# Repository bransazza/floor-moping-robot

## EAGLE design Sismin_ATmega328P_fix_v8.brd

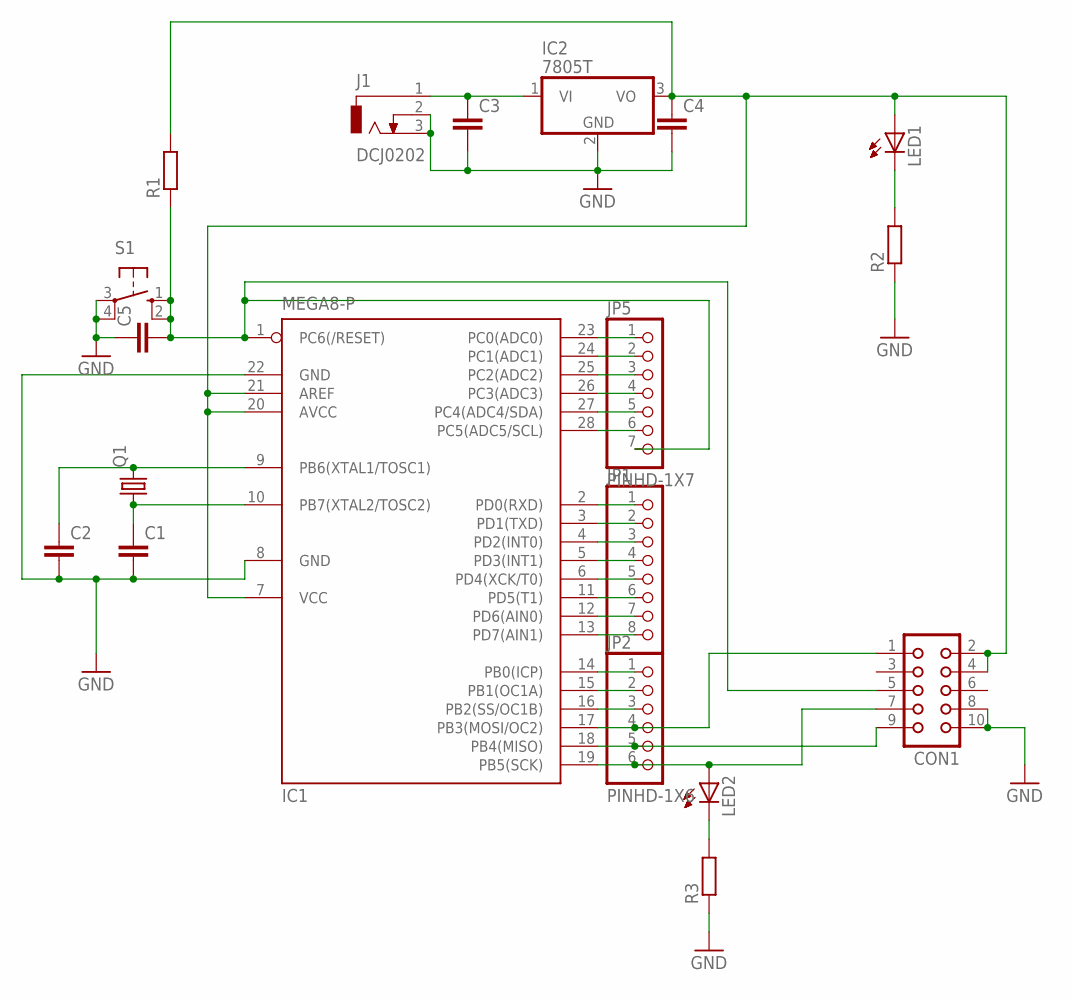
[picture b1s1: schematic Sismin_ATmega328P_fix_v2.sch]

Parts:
C1, C2, C3, C4, C5: C-EU025-030X050; C025-030X050
CON1: CON10
IC1: MEGA8-P; DIL28-3
IC2: 7805T; TO220H
J1: DCJ0202
JP1: PINHD-1X8; 1X08
JP2: PINHD-1X6; 1X06
JP5: PINHD-1X7; 1X07
LED1, LED2: LED3MM
Q1: CRYSTALHC49U-V; HC49U-V
R1, R2, R3: R-EU_0204/7; 0204/7
S1: 10-XX; B3F-10XX

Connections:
GND: C1.2, C2.2, C3.2, C4.2, C5.1, CON1.8, CON1.10, IC1.8 (GND), IC1.22 (GND), IC2.2 (GND), J1.2, J1.3, R2.1, R3.1, S1.3, S1.4 (P1)
unnamed: C3.1, IC2.1 (VI), J1.1
unnamed: C4.1, CON1.2, CON1.4, IC1.7 (VCC), IC1.20 (AVCC), IC1.21 (AREF), IC2.3 (VO), LED1.A, R1.2
unnamed: LED1.K (C), R2.2
unnamed: LED2.K (C), R3.2
unnamed: IC1.23 (PC0(ADC0)), JP5.1
unnamed: IC1.24 (PC1(ADC1)), JP5.2
unnamed: IC1.25 (PC2(ADC2)), JP5.3
unnamed: IC1.26 (PC3(ADC3)), JP5.4
unnamed: IC1.27 (PC4(ADC4/SDA)), JP5.5
unnamed: IC1.28 (PC5(ADC5/SCL)), JP5.6
unnamed: IC1.2 (PD0(RXD)), JP1.1
unnamed: CON1.1, IC1.17 (PB3(MOSI/OC2)), JP2.4
unnamed: CON1.9, IC1.18 (PB4(MISO)), JP2.5
unnamed: IC1.3 (PD1(TXD)), JP1.2
unnamed: IC1.4 (PD2(INT0)), JP1.3
unnamed: IC1.5 (PD3(INT1)), JP1.4
unnamed: IC1.6 (PD4(XCK/T0)), JP1.5
unnamed: IC1.11 (PD5(T1)), JP1.6
unnamed: IC1.12 (PD6(AIN0)), JP1.7
unnamed: IC1.13 (PD7(AIN1)), JP1.8
unnamed: C2.1, IC1.9 (PB6(XTAL1/TOSC1)), Q1.2
unnamed: C1.1, IC1.10 (PB7(XTAL2/TOSC2)), Q1.1
unnamed: C5.2, CON1.5, IC1.1 (PC6(/RESET)), JP5.7, R1.1, S1.1 (S), S1.2 (S1)
unnamed: IC1.14 (PB0(ICP)), JP2.1
unnamed: IC1.15 (PB1(OC1A)), JP2.2
unnamed: IC1.16 (PB2(SS/OC1B)), JP2.3
unnamed: CON1.7, IC1.19 (PB5(SCK)), JP2.6, LED2.A

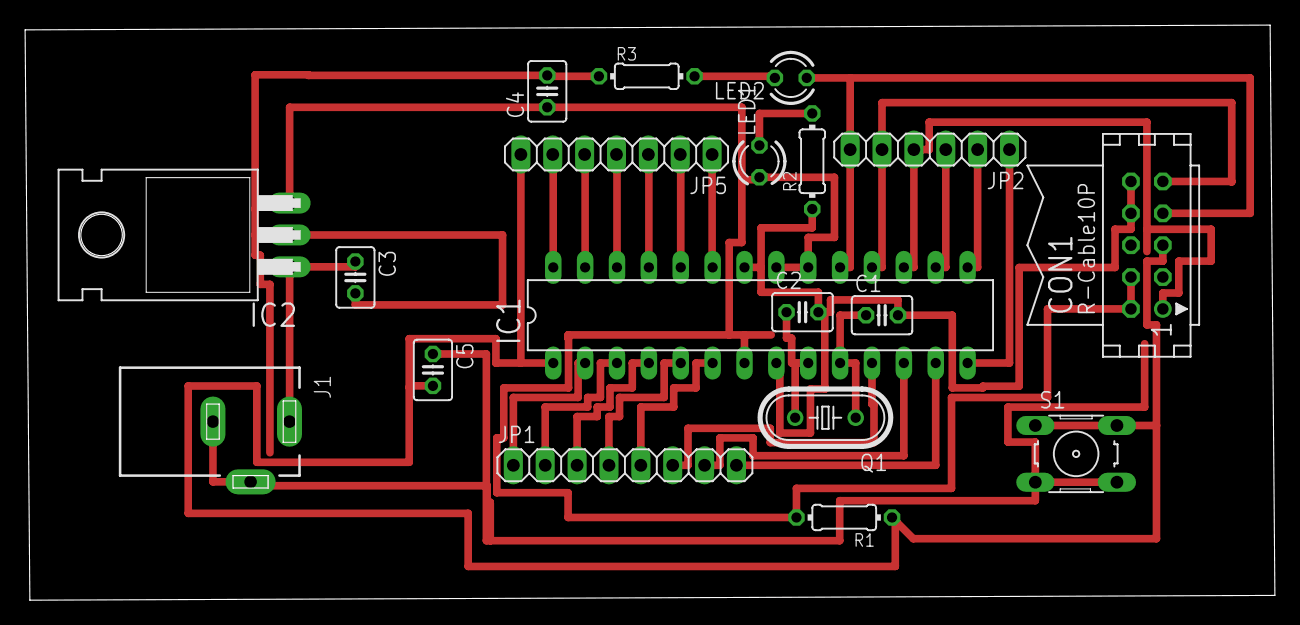
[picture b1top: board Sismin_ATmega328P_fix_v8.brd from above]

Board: 2 copper layers, 99.6 x 45.8 mm, 19 parts (0 on the bottom side), 28 nets.

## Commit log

2024-08-08 robotics-commit
